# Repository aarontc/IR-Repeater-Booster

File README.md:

# IR Repeater Booster
This is a small electronic circuit to relay signals from an IR repeater over category (5/6) cabling using differential signalling to achieve very long runs.

It was based upon the ["Tunteil IR Remote Control Repeater"] from Amazon, sourced around December 2020. 
The device has a powered IR receiver that seems to accommodate a range of frequencies, operating from 5V DC and providing
an open-collector output. It then uses buffer transistors to drive up to 6 pairs of IR LEDs with a low value series resistor.

The IR receiver uses a 3.5mm TRS connector, where tip is output, ring is 5V, and sleeve is ground.

The Repeater Booster is designed to operate between the IR receiver and the "repeater" unit. 

This board is designed to be as inexpensive as is reasonably possible using JLCPCB's assembly service. 

## Design Notes

* 12V DC input is optional at one end, the cat5/6 connection can be used to carry 12V to the other end.
* Boards must be used in pairs, one as an input and one as an output.
* 120-ohm termination is required at both ends of the bus. If you are connecting more than one RX board, cut the temrination jumper on the middle board(s) to prevent overburdening the differential drivers.
 
["Tunteil IR Remote Control Repeater"]: https://amzn.to/3bettCj

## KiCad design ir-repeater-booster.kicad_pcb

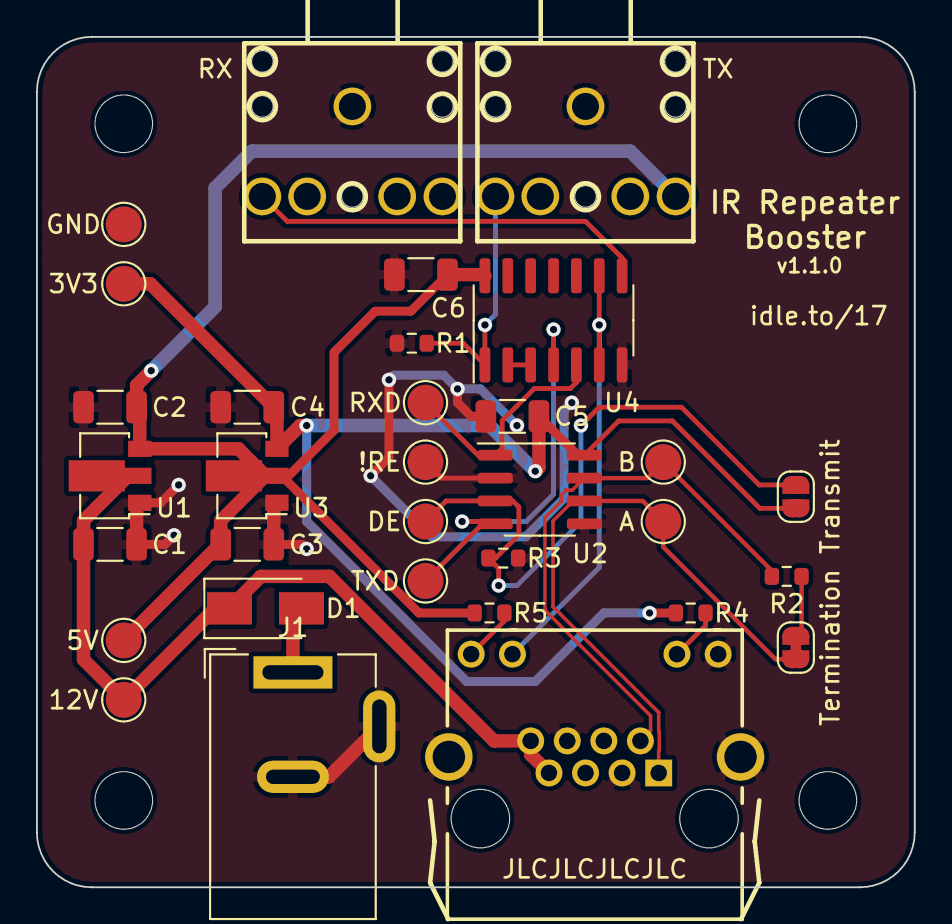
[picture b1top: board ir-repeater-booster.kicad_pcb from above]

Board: 2 copper layers, 48.8 x 47.2 mm, 36 parts (0 on the bottom side), 17 nets.

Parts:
C1, C2, C3, C4, C5, C6: 10u; C_1206_3216Metric
D1: SS14; D_SMA
H1, H2, H3, H4: MountingHole; MountingHole_3.2mm_M3
J1: DC_IN; BarrelJack_Wuerth_6941xx301002
J2: RJ45_LED_Shielded; RJ45-TH_B-1-1
JP1: Termination; SolderJumper-2_P1.3mm_Bridged_RoundedPad1.0x1.5mm
JP2: Transmit; SolderJumper-2_P1.3mm_Open_RoundedPad1.0x1.5mm
R1: 1k; R_0603_1608Metric
R2: 120; R_0603_1608Metric
R3: 10k; R_0603_1608Metric
R4: 560; R_0603_1608Metric
R5: 1k2; R_0603_1608Metric
RX1: PJ-307C; AUDIO-TH_PJ307C
TP1: !RE; TestPoint_Pad_D2.0mm
TP2: DE; TestPoint_Pad_D2.0mm
TP3: RXD; TestPoint_Pad_D2.0mm
TP4: TXD; TestPoint_Pad_D2.0mm
TP5: A; TestPoint_Pad_D2.0mm
TP6: B; TestPoint_Pad_D2.0mm
TP7: 12V; TestPoint_Pad_D2.0mm
TP8: 5V; TestPoint_Pad_D2.0mm
TP9: 3V3; TestPoint_Pad_D2.0mm
TP10: GND; TestPoint_Pad_D2.0mm
TX1: PJ-307C; AUDIO-TH_PJ307C
U1: HT7550-1; SOT-89-3
U2: ST3485EBDR; SOIC-8_3.9x4.9mm_P1.27mm
U3: HT7533-1; SOT-89-3
U4: 74HC14; SOIC-14_3.9x8.7mm_P1.27mm

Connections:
+3V3: C4.1, C5.1, JP2.1, R4.1, TP9.1, U2.8, U3.3
+5V: C2.1, C3.1, C6.1, R5.1, TP8.1, TX1.2, U1.3, U3.2, U4.14
+12V: C1.1, D1.1, J2.7, J2.8, TP7.1, U1.2
/485+: J2.1, JP1.1, TP5.1, U2.6
/485-: J2.2, R2.2, TP6.1, U2.7
/DE: JP2.2, R3.1, TP2.1, U2.3
/GLED_A: J2.10, R4.2
/RXD: TP3.1, U2.1, U4.5
/RXOUT: RX1.5, U4.8
/TXD: TP4.1, U2.4, U4.4
/YLED_A: J2.12, R5.2
/YLED_C: J2.11, U4.6, U4.9
GND: C1.2, C2.2, C3.2, C4.2, C5.2, C6.2, J1.2, J1.3, J2.3, J2.6, J2.9, J2.SH, R1.1, R3.2, RX1.1, TP1.1, TP10.1, TX1.1, U1.1, U2.2, U2.5, U3.1, U4.7
unnamed: D1.2, J1.1
unnamed: JP1.2, R2.1
unnamed: R1.2, TX1.5, U4.1
unnamed: U4.2, U4.3

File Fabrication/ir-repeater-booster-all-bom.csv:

Reference, Value, Footprint, Datasheet, Description, JEDEC Package Name, Manufacturer Name, Manufacturer Part Number, Vendor 1 Link, Vendor 1 Name, Vendor 1 Part Number, Vendor 1 Price @1, Vendor 1 Pricing Date
"U2","ST3485EBDR","Package_SO:SOIC-8_3.9x4.9mm_P1.27mm","https://datasheet.lcsc.com/szlcsc/1810181648_STMicroelectron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","transceiver RS422, RS485 1/1 15Mbps SO-8 RS-485/RS-422 ICs RoHS","SO-8","STMicroelectronics","ST3485EBDR","https://lcsc.com/product-detail/RS-485-RS-422-ICs_STMicroele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","LCSC","C75809","$0.7574","2021-03-03"
"J1","DC_IN","Connector_BarrelJack:BarrelJack_Wuerth_6941xx301002","~"
"J2","RJ45_LED_Shielded","Footprints:RJ45-TH_B-1-1","https://datasheet.lcsc.com/szlcsc/1811141116_BOOMELE-Boom-Pr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","RJ45 12 1 Through Hole Ethernet Connectors/Modular Connectors (RJ45 RJ11) RoHS","","BOOMELE(Boom Precision Elec)","RJ45-B-1*1","https://lcsc.com/product-detail/Ethernet-Connectors-Modular-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","LCSC","C138392","$0.2518","2021-03-03"
"JP1","Termination","Jumper:SolderJumper-2_P1.3mm_Bridged_RoundedPad1.0x1.5mm","~"
"R2","120","Resistor_SMD:R_0603_1608Metric","https://datasheet.lcsc.com/szlcsc/1811021215_UNI-ROYAL-Uniro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","120Ω ±1% 0.1W ±100ppm/℃ 0603 Chip Resistor - Surface Mount RoHS","0603","UNI-ROYAL(Uniroyal Elec)","0603WAF1200T5E","https://lcsc.com/product-detail/Chip-Resistor-Surface-Mount_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","LCSC","C22787","$0.0014","2021-03-03"
"U1","HT7550-1","Package_TO_SOT_SMD:SOT-89-3","https://datasheet.lcsc.com/szlcsc/1811061932_Holtek-Semicon-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","Fixed 30V 3.3V 55mV @ 1mA SOT-89(SOT-89-3) Dropout Regulators(LDO) RoHS","SOT-89-3","Holtek Semicon","HT7550-1","https://lcsc.com/product-detail/Low-Dropout-Regulators-LDO_H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","LCSC","C16106","$0.1669","2021-03-03"
"C1","10u","Capacitor_SMD:C_1206_3216Metric","https://datasheet.lcsc.com/szlcsc/1810221112_Samsung-Electro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","10uF ±10% 50V X5R 1206 Multilayer Ceramic Capacitors MLCC - SMD/SMT RoHS","1206","Samsung Electro-Mechanics","CL31A106KBHNNNE","https://lcsc.com/product-detail/Multilayer-Ceramic-Capacitor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","LCSC","C13585","$0.0611","2021-03-03"
"C2","10u","Capacitor_SMD:C_1206_3216Metric","https://datasheet.lcsc.com/szlcsc/1810221112_Samsung-Electro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","10uF ±10% 50V X5R 1206 Multilayer Ceramic Capacitors MLCC - SMD/SMT RoHS","1206","Samsung Electro-Mechanics","CL31A106KBHNNNE","https://lcsc.com/product-detail/Multilayer-Ceramic-Capacitor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","LCSC","C13585","$0.0611","2021-03-03"
"TX1","PJ-307C","Footprints:AUDIO-TH_PJ307C","https://datasheet.lcsc.com/szlcsc/1811040611_BOOMELE-Boom-Pr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","3.5mm Plug-in headphone holder 5 Female Horizontal 3.5mm Audio & Video Connectors RoHS","","BOOMELE(Boom Precision Elec)","PJ-307C","https://lcsc.com/product-detail/Audio-Video-Connectors_BOOME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","LCSC","C16684","$0.0422","2021-03-03"
"R4","270","Resistor_SMD:R_0805_2012Metric","https://datasheet.lcsc.com/szlcsc/1810301813_UNI-ROYAL-Uniro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","270Ω ±1% 0.125W ±100ppm/℃ 0805 Chip Resistor - Surface Mount RoHS","0805","UNI-ROYAL(Uniroyal Elec)","0805W8F2700T5E","https://lcsc.com/product-detail/Chip-Resistor-Surface-Mount_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","LCSC","C17590","$0.0027","2021-03-03"
"U3","HT7533-1","Package_TO_SOT_SMD:SOT-89-3","https://datasheet.lcsc.com/szlcsc/1811062113_Holtek-Semicon-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","Fixed 30V 3.3V 55mV @ 1mA SOT-89(SOT-89-3) Dropout Regulators(LDO) RoHS","SOT-89-3","Holtek Semicon","HT7533-1","https://lcsc.com/product-detail/Low-Dropout-Regulators-LDO_H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","LCSC","C14289","$0.1494","2021-03-03"
"C3","10u","Capacitor_SMD:C_1206_3216Metric","https://datasheet.lcsc.com/szlcsc/1810221112_Samsung-Electro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","10uF ±10% 50V X5R 1206 Multilayer Ceramic Capacitors MLCC - SMD/SMT RoHS","1206","Samsung Electro-Mechanics","CL31A106KBHNNNE","https://lcsc.com/product-detail/Multilayer-Ceramic-Capacitor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","LCSC","C13585","$0.0611","2021-03-03"
"C4","10u","Capacitor_SMD:C_1206_3216Metric","https://datasheet.lcsc.com/szlcsc/1810221112_Samsung-Electro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","10uF ±10% 50V X5R 1206 Multilayer Ceramic Capacitors MLCC - SMD/SMT RoHS","1206","Samsung Electro-Mechanics","CL31A106KBHNNNE","https://lcsc.com/product-detail/Multilayer-Ceramic-Capacitor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","LCSC","C13585","$0.0611","2021-03-03"
"R1","1k","Resistor_SMD:R_0603_1608Metric","https://datasheet.lcsc.com/szlcsc/1811141223_UNI-ROYAL-Uniro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","1kΩ ±1% 0.1W ±100ppm/℃ 0603 Chip Resistor - Surface Mount RoHS","0603","UNI-ROYAL(Uniroyal Elec)","0603WAF1001T5E","https://lcsc.com/product-detail/Chip-Resistor-Surface-Mount_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","LCSC","C21190","$0.0015","2013-03-03"
"JP2","Transmit","Jumper:SolderJumper-2_P1.3mm_Open_RoundedPad1.0x1.5mm","~"
"R3","10k","Resistor_SMD:R_0603_1608Metric","https://datasheet.lcsc.com/szlcsc/1811062009_UNI-ROYAL-Uniro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","10kΩ ±1% 0.1W ±100ppm/℃ 0603 Chip Resistor - Surface Mount RoHS","0603","UNI-ROYAL(Uniroyal Elec)","0603WAF1002T5E","https://lcsc.com/product-detail/Chip-Resistor-Surface-Mount_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","LCSC","C25804","$0.0016","2021-03-03"
"R5","270","Resistor_SMD:R_0805_2012Metric","https://datasheet.lcsc.com/szlcsc/1810301813_UNI-ROYAL-Uniro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","270Ω ±1% 0.125W ±100ppm/℃ 0805 Chip Resistor - Surface Mount RoHS","0805","UNI-ROYAL(Uniroyal Elec)","0805W8F2700T5E","https://lcsc.com/product-detail/Chip-Resistor-Surface-Mount_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","LCSC","C17590","$0.0027","2021-03-03"
"D1","SS14","Diode_SMD:D_SMA","https://datasheet.lcsc.com/szlcsc/2007141104_MDD-Microdiode-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","40V 1A 550mV @ 1A SMA(DO-214AC) Schottky Barrier Diodes (SBD) RoHS","DO-214AC","MDD(Microdiode Electronics)","SS14","https://lcsc.com/product-detail/Schottky-Barrier-Diodes-SBD_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","LCSC","C2480","$0.0164","2021-03-03"
"D3","SS14","Diode_SMD:D_SMA","https://datasheet.lcsc.com/szlcsc/2007141104_MDD-Microdiode-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","40V 1A 550mV @ 1A SMA(DO-214AC) Schottky Barrier Diodes (SBD) RoHS","DO-214AC","MDD(Microdiode Electronics)","SS14","https://lcsc.com/product-detail/Schottky-Barrier-Diodes-SBD_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","LCSC","C2480","$0.0164","2021-03-03"
"D2","SS14","Diode_SMD:D_SMA","https://datasheet.lcsc.com/szlcsc/2007141104_MDD-Microdiode-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","40V 1A 550mV @ 1A SMA(DO-214AC) Schottky Barrier Diodes (SBD) RoHS","DO-214AC","MDD(Microdiode Electronics)","SS14","https://lcsc.com/product-detail/Schottky-Barrier-Diodes-SBD_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","LCSC","C2480","$0.0164","2021-03-03"
"RX1","PJ-307C","Footprints:AUDIO-TH_PJ307C","https://datasheet.lcsc.com/szlcsc/1811040611_BOOMELE-Boom-Pr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","3.5mm Plug-in headphone holder 5 Female Horizontal 3.5mm Audio & Video Connectors RoHS","","BOOMELE(Boom Precision Elec)","PJ-307C","https://lcsc.com/product-detail/Audio-Video-Connectors_BOOME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","LCSC","C16684","$0.0422","2021-03-03"
"H1","MountingHole","MountingHole:MountingHole_3.2mm_M3","~"
"H2","MountingHole","MountingHole:MountingHole_3.2mm_M3","~"
"H3","MountingHole","MountingHole:MountingHole_3.2mm_M3","~"
"H4","MountingHole","MountingHole:MountingHole_3.2mm_M3","~"
"JP3","REDE","Jumper:SolderJumper-2_P1.3mm_Bridged_RoundedPad1.0x1.5mm","~"
"TP9","3V3","TestPoint:TestPoint_Pad_D2.0mm","~"
"TP8","5V","TestPoint:TestPoint_Pad_D2.0mm","~"
"TP7","12V","TestPoint:TestPoint_Pad_D2.0mm","~"
"TP6","B","TestPoint:TestPoint_Pad_D2.0mm","~"
"TP5","A","TestPoint:TestPoint_Pad_D2.0mm","~"
"TP4","TXD","TestPoint:TestPoint_Pad_D2.0mm","~"
"TP3","RXD","TestPoint:TestPoint_Pad_D2.0mm","~"
"TP2","DE","TestPoint:TestPoint_Pad_D2.0mm","~"
"TP1","!RE","TestPoint:TestPoint_Pad_D2.0mm","~"

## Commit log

2021-03-04 Initial commit to backup schematic, should be ready for PCB layout
2021-03-06 Stashing progress
2021-03-06 Finishing work for 1.0.0 to fabricate
2021-03-21 1.1.0 updates
2021-03-21 Fix component position file for JLCPCB assembly
2021-04-02 Updates to notes in README.
